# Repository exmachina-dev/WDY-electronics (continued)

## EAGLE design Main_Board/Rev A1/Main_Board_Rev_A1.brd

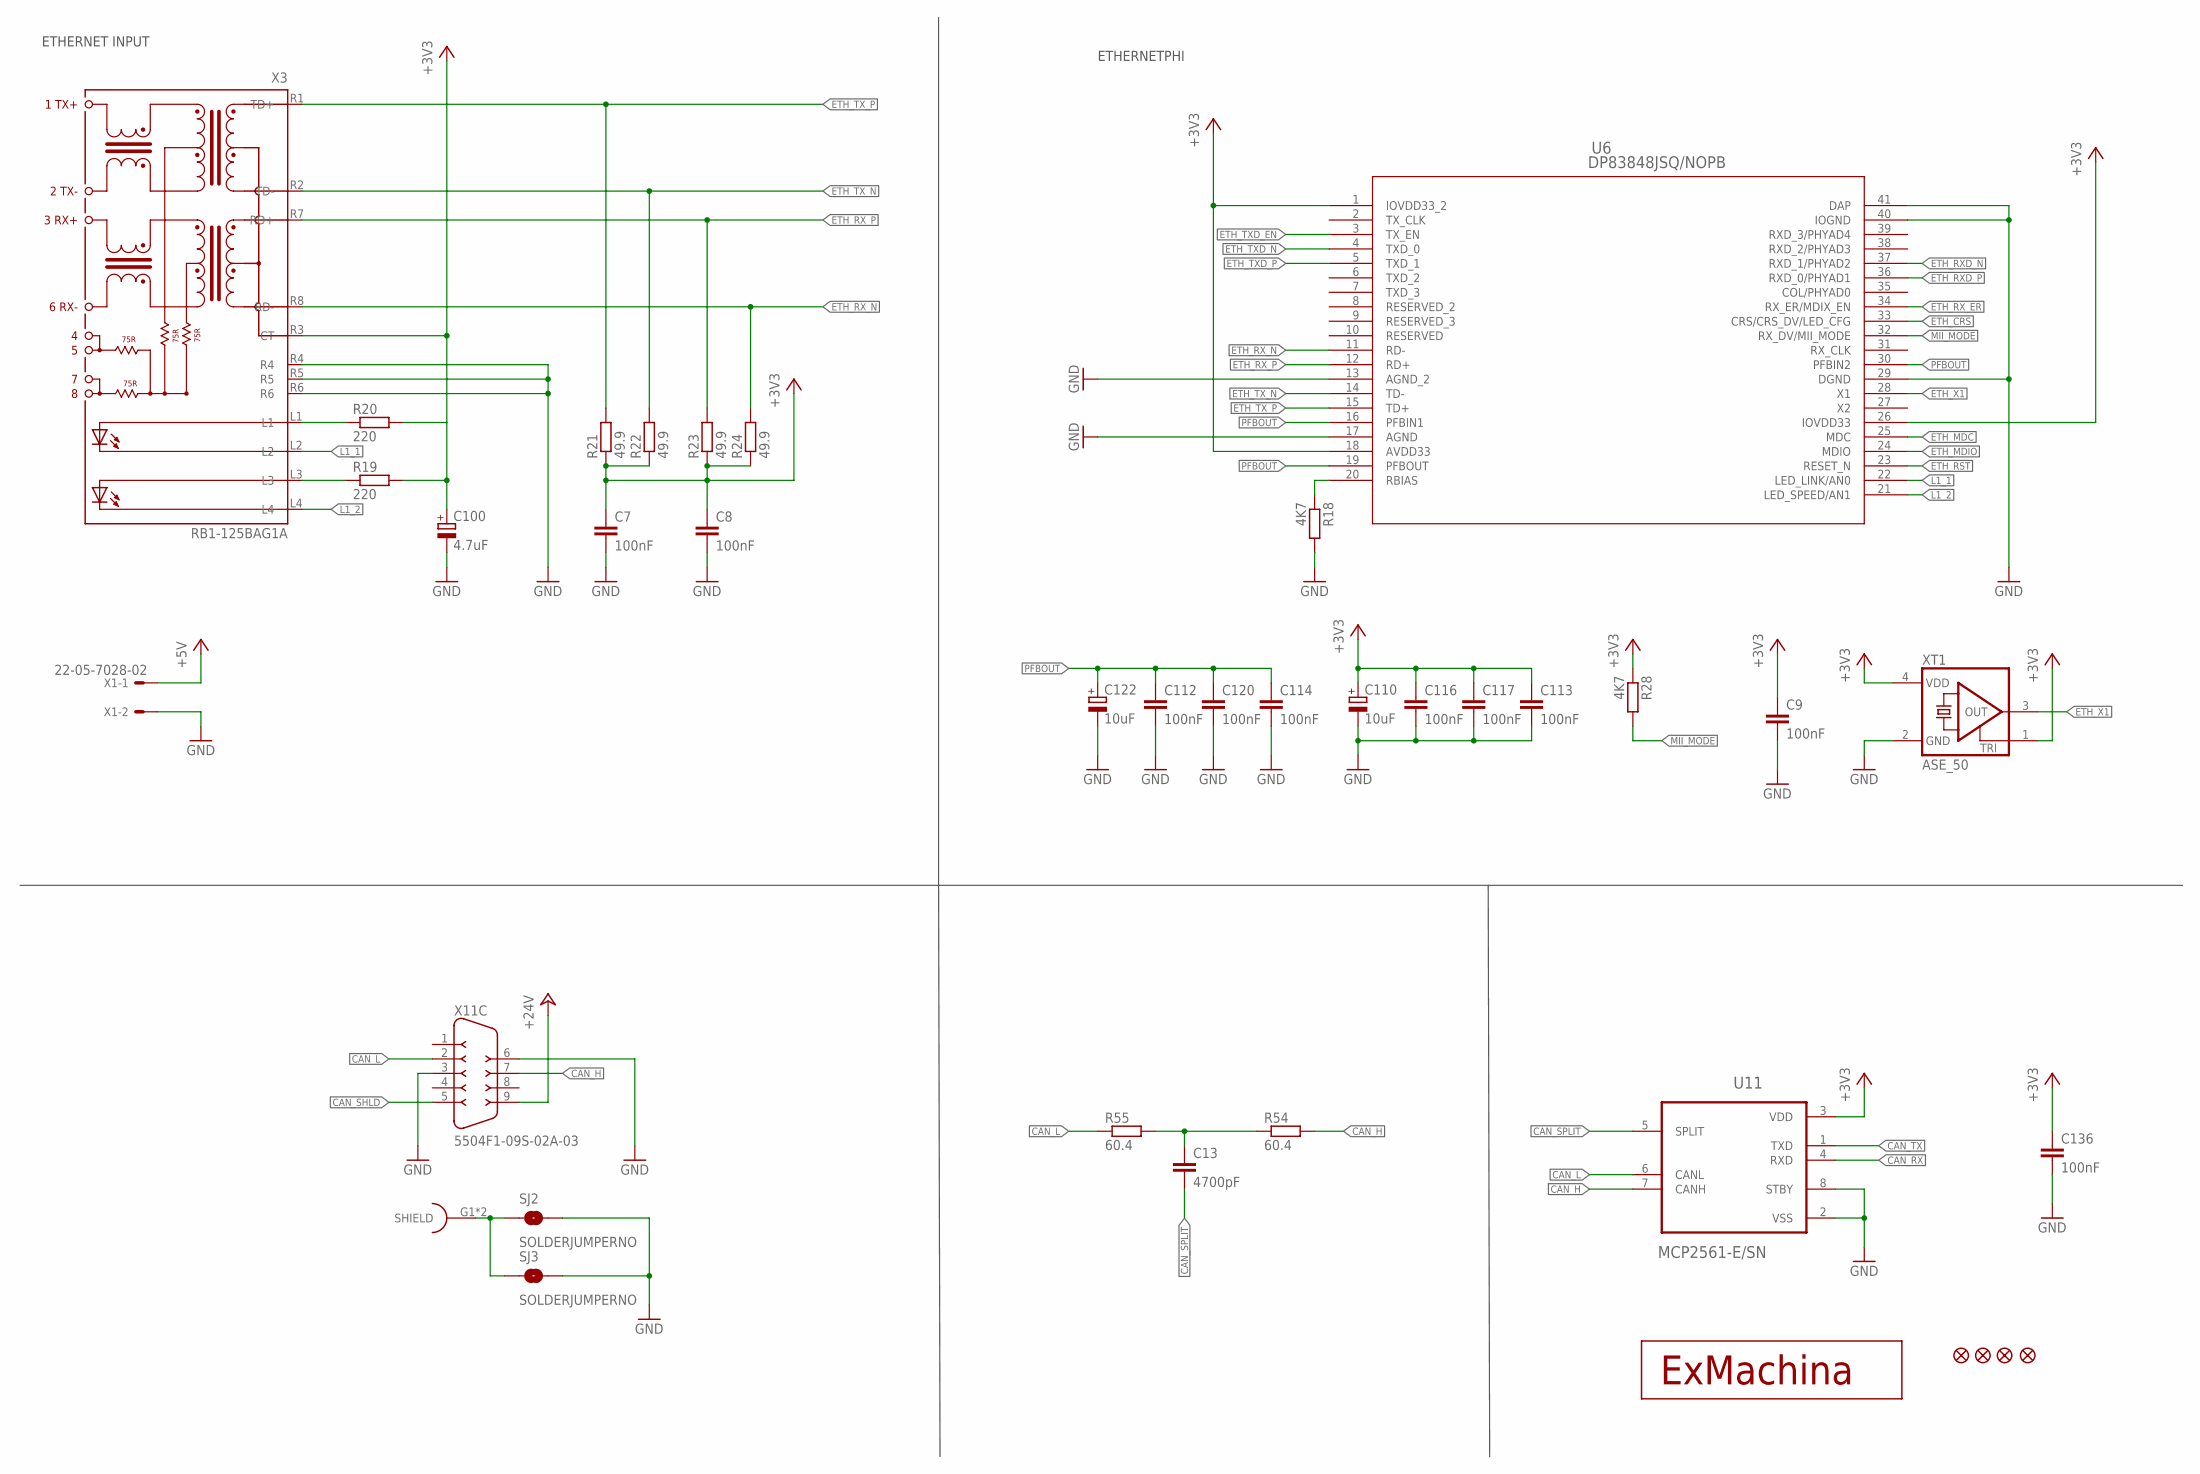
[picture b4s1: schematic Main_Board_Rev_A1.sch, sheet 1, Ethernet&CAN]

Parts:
C7, C8, C9, C112, C113, C114, C116, C117, C120, C136: 100nF; C0603
C13: 4700pF; C0603
C100: 4.7uF; CT3216
C110, C122: 10uF; CT3216
JP1, JP2, JP4, JP5: FIDUCIAL1X2; FIDUCIAL-1X2
R18, R28: 4K7; R0603
R19, R20: 220; R0603
R21, R22, R23, R24: 49.9; R0603
R54, R55: 60.4; R0603
SJ2, SJ3: SOLDERJUMPERNO; SJ_2S-NO
U6: DP83848JSQ/NOPB; SQA40B
U11: MCP2561-E/SN; SOIC127P600X175-8N
U$2: EXMACHINA-LOGO-NAME; EXM-LOGO-BASELINE
X1: 22-05-7028-02; 7395-02
X3: RB1-125BAG1A; WIZNET_RB1-125BAG1A
X11: 5504F1-09S-02A-03; 5504F1-09S-02A
XT1: ASE_50; ASE

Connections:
+3V3: C7.1, C8.1, C9.1, C100.+, C110.+, C113.1, C116.1, C117.1, C136.1, R19.2, R20.2, R21.1, R22.1, R23.1, R24.1, R28.1, U6.1 (IOVDD33_2), U6.18 (AVDD33), U6.26 (IOVDD33), U11.3 (VDD), X3.R3 (CT), XT1.1 (TRI), XT1.4 (VDD); also elsewhere on the board
+5V: X1.1; also elsewhere on the board
+24V: X11.9; also elsewhere on the board
CAN_H: R54.2, U11.7 (CANH), X11.7
CAN_L: R55.1, U11.6 (CANL), X11.2
CAN_RX: U11.4 (RXD); also elsewhere on the board
CAN_SHLD: X11.5
CAN_SPLIT: C13.2, U11.5 (SPLIT)
CAN_TX: U11.1 (TXD); also elsewhere on the board
ETH_CRS: U6.33 (CRS/CRS_DV/LED_CFG); also elsewhere on the board
ETH_MDC: U6.25 (MDC); also elsewhere on the board
ETH_MDIO: U6.24 (MDIO); also elsewhere on the board
ETH_RST: U6.23 (RESET_N)
ETH_RXD_N: U6.37 (RXD_1/PHYAD2); also elsewhere on the board
ETH_RXD_P: U6.36 (RXD_0/PHYAD1); also elsewhere on the board
ETH_RX_ER: U6.34 (RX_ER/MDIX_EN); also elsewhere on the board
ETH_RX_N: R24.2, U6.11 (RD-), X3.R8 (RD-)
ETH_RX_P: R23.2, U6.12 (RD+), X3.R7 (RD+)
ETH_TXD_EN: U6.3 (TX_EN); also elsewhere on the board
ETH_TXD_N: U6.4 (TXD_0); also elsewhere on the board
ETH_TXD_P: U6.5 (TXD_1); also elsewhere on the board
ETH_TX_N: R22.2, U6.14 (TD-), X3.R2 (TD-)
ETH_TX_P: R21.2, U6.15 (TD+), X3.R1 (TD+)
ETH_X1: U6.28 (X1), XT1.3 (OUT)
GND: C7.2, C8.2, C9.2, C100.-, C110.-, C112.2, C113.2, C114.2, C116.2, C117.2, C120.2, C122.-, C136.2, R18.2, SJ2.2, SJ3.2, U6.13 (AGND_2), U6.17 (AGND), U6.29 (DGND), U6.40 (IOGND), U6.41 (DAP), U11.2 (VSS), U11.8 (STBY), X1.2, X3.R4, X3.R5, X3.R6, X11.3, X11.6, XT1.2 (GND); also elsewhere on the board
L1_1: U6.22 (LED_LINK/AN0), X3.L2
L1_2: U6.21 (LED_SPEED/AN1), X3.L4
MII_MODE: R28.2, U6.32 (RX_DV/MII_MODE)
unnamed: C13.1, R54.1, R55.2
unnamed: R18.1, U6.20 (RBIAS)
unnamed: SJ2.1, SJ3.1, X11.G1 (SHIELD), X11.G2 (SHIELD)
unnamed: R20.1, X3.L1
unnamed: R19.1, X3.L3
PFBOUT: C112.1, C114.1, C120.1, C122.+, U6.16 (PFBIN1), U6.19 (PFBOUT), U6.30 (PFBIN2)

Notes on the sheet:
ETHERNET INPUT
ETHERNETPHI

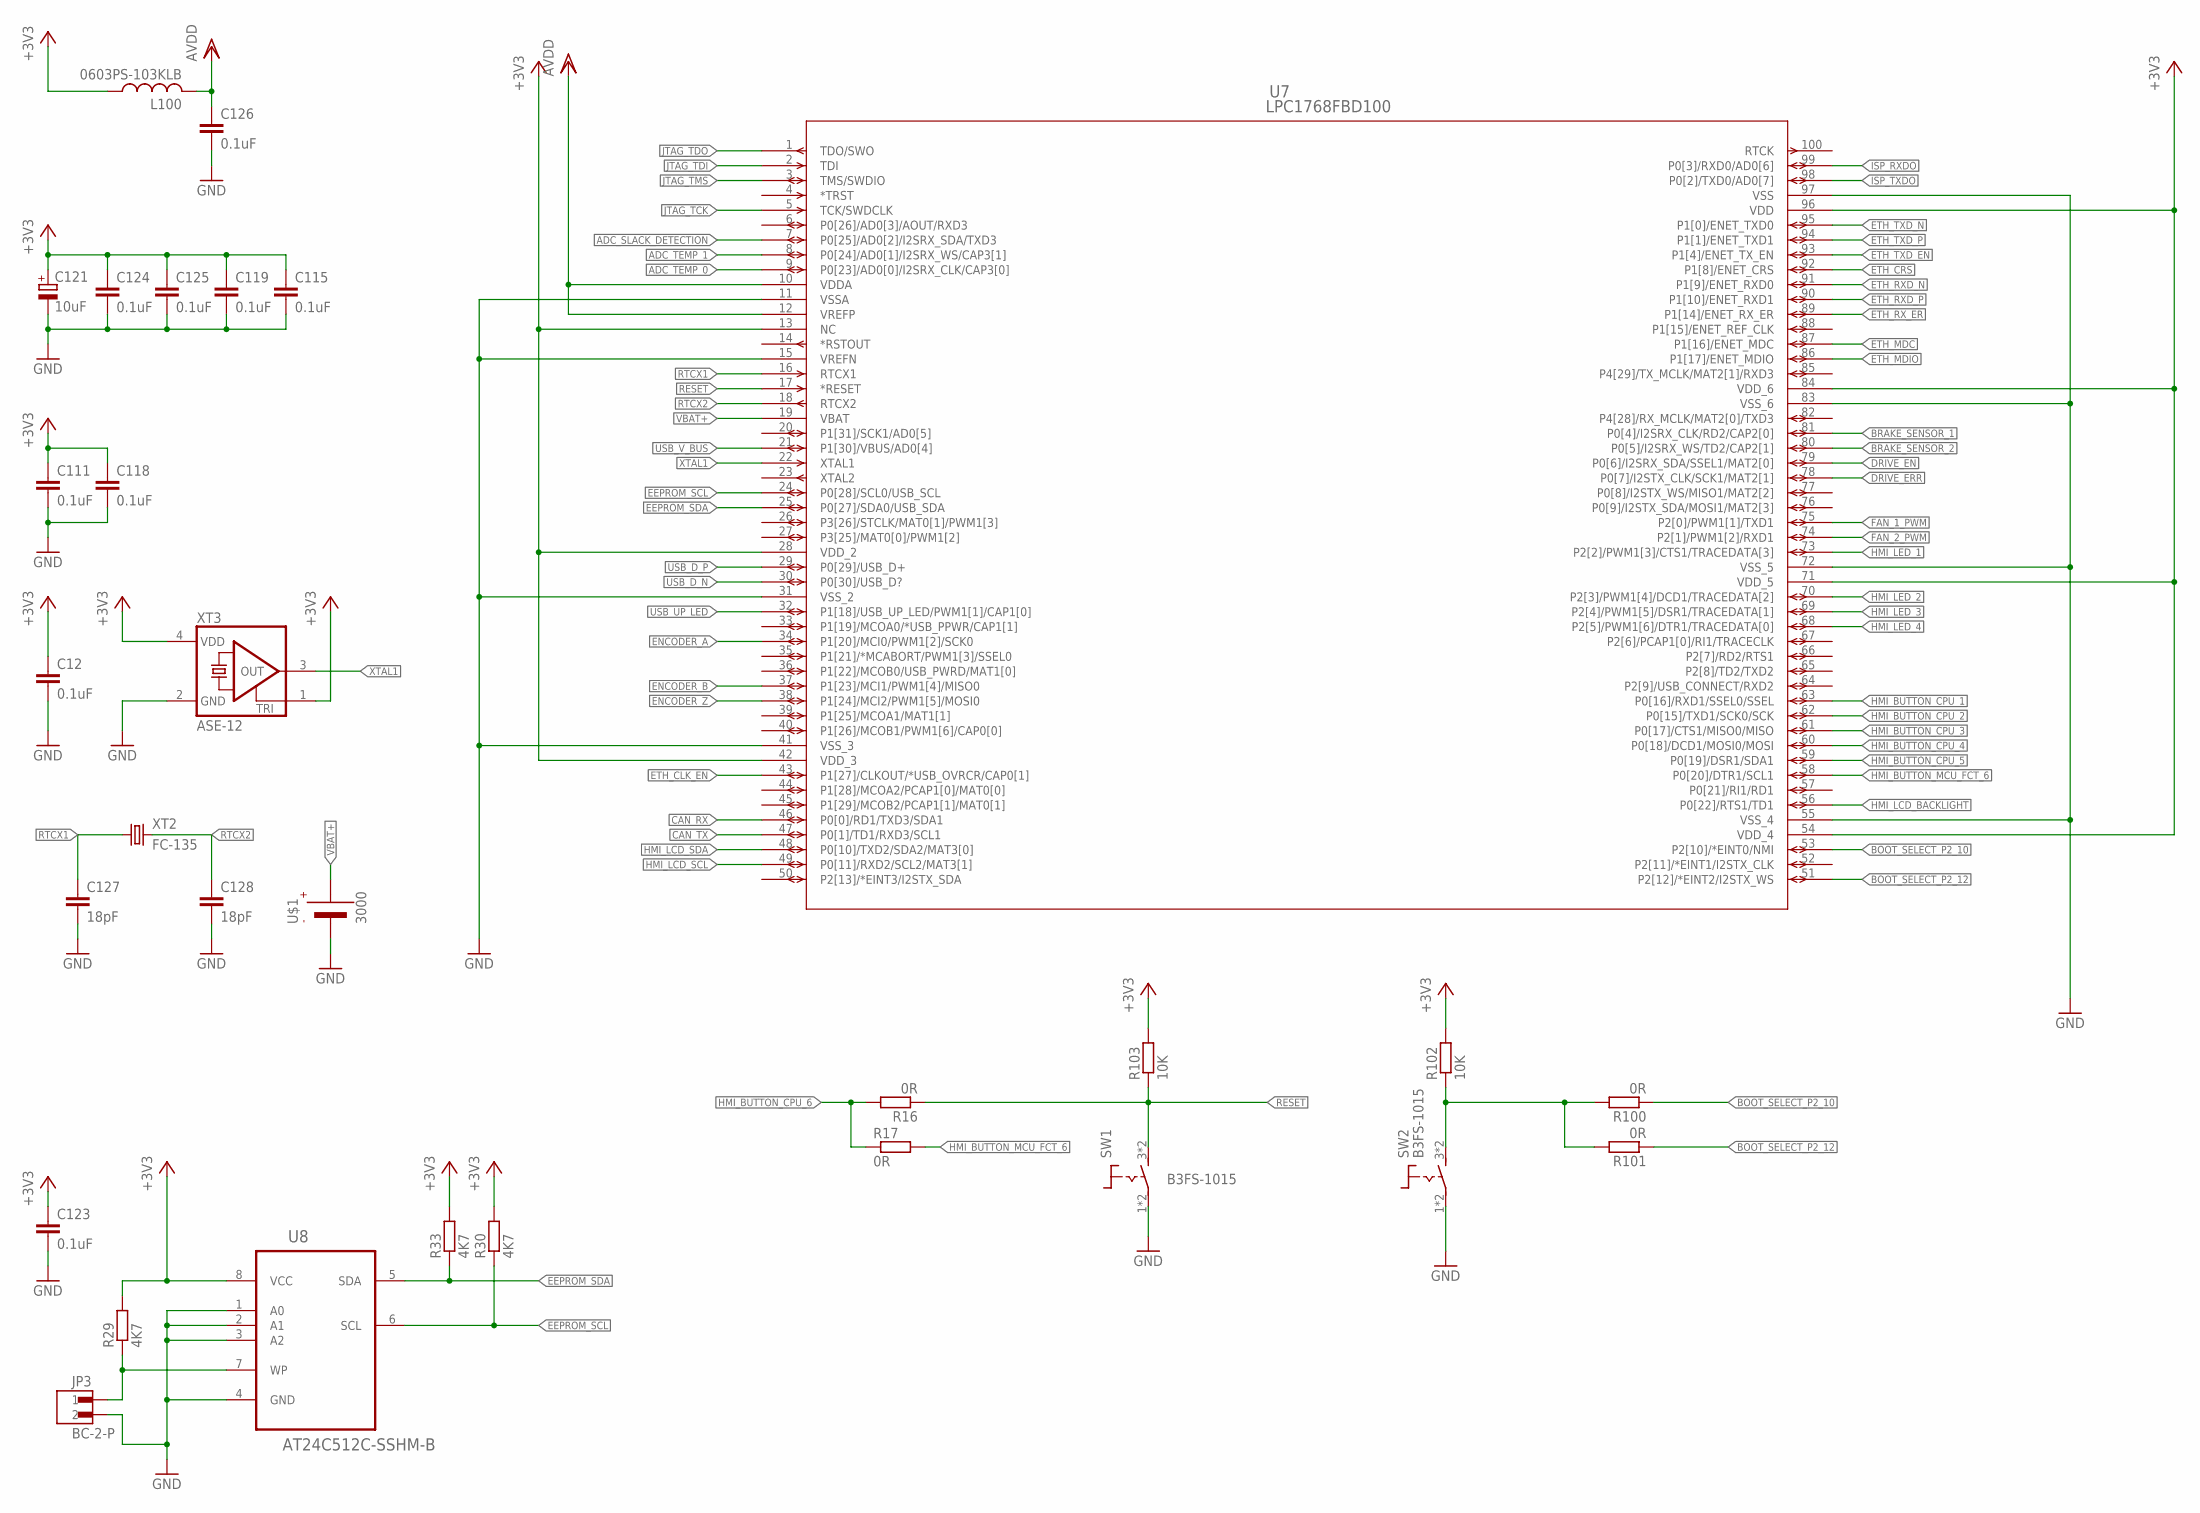
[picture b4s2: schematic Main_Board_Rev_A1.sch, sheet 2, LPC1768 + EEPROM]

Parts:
C12, C111, C115, C118, C119, C123, C124, C125, C126: 0.1uF; C0603
C121: 10uF; CT3216
C127, C128: 18pF; C0603
JP3: BC-2-P
L100: 0603PS-103KLB; 0603
R16, R17, R100, R101: 0R; R0603
R29, R30, R33: 4K7; R0603
R102, R103: 10K; R0603
SW1, SW2: B3FS-1015; B3FS
U7: LPC1768FBD100; SOT407-1
U8: AT24C512C-SSHM-B; SOIC127P600X175-8N
U$1: 3000
XT2: FC-135
XT3: ASE-12; ASE

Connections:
+3V3: C12.1, C111.1, C115.1, C118.1, C119.1, C121.+, C123.1, C124.1, C125.1, L100.P$1 (1), R29.2, R30.2, R33.2, R102.2, R103.2, U7.13 (NC), U7.28 (VDD_2), U7.42 (VDD_3), U7.54 (VDD_4), U7.71 (VDD_5), U7.84 (VDD_6), U7.96 (VDD), U8.8 (VCC), XT3.1 (TRI), XT3.4 (VDD); also elsewhere on the board
ADC_SLACK_DETECTION: U7.7 (P0[25]/AD0[2]/I2SRX_SDA/TXD3); also elsewhere on the board
ADC_TEMP_0: U7.9 (P0[23]/AD0[0]/I2SRX_CLK/CAP3[0]); also elsewhere on the board
ADC_TEMP_1: U7.8 (P0[24]/AD0[1]/I2SRX_WS/CAP3[1]); also elsewhere on the board
AVDD: C126.1, L100.P$2 (2), U7.10 (VDDA), U7.12 (VREFP); also elsewhere on the board
BOOT_SELECT_P2_10: R100.1, U7.53 (P2[10]/*EINT0/NMI)
BOOT_SELECT_P2_12: R101.1, U7.51 (P2[12]/*EINT2/I2STX_WS)
BRAKE_SENSOR_1: U7.81 (P0[4]/I2SRX_CLK/RD2/CAP2[0]); also elsewhere on the board
BRAKE_SENSOR_2: U7.80 (P0[5]/I2SRX_WS/TD2/CAP2[1]); also elsewhere on the board
CAN_RX: U7.46 (P0[0]/RD1/TXD3/SDA1); also elsewhere on the board
CAN_TX: U7.47 (P0[1]/TD1/RXD3/SCL1); also elsewhere on the board
DRIVE_EN: U7.79 (P0[6]/I2SRX_SDA/SSEL1/MAT2[0]); also elsewhere on the board
DRIVE_ERR: U7.78 (P0[7]/I2STX_CLK/SCK1/MAT2[1]); also elsewhere on the board
EEPROM_SCL: R30.1, U7.24 (P0[28]/SCL0/USB_SCL), U8.6 (SCL)
EEPROM_SDA: R33.1, U7.25 (P0[27]/SDA0/USB_SDA), U8.5 (SDA)
ENCODER_A: U7.34 (P1[20]/MCI0/PWM1[2]/SCK0); also elsewhere on the board
ENCODER_B: U7.37 (P1[23]/MCI1/PWM1[4]/MISO0); also elsewhere on the board
ENCODER_Z: U7.38 (P1[24]/MCI2/PWM1[5]/MOSI0); also elsewhere on the board
ETH_CLK_EN: U7.43 (P1[27]/CLKOUT/*USB_OVRCR/CAP0[1])
ETH_CRS: U7.92 (P1[8]/ENET_CRS); also elsewhere on the board
ETH_MDC: U7.87 (P1[16]/ENET_MDC); also elsewhere on the board
ETH_MDIO: U7.86 (P1[17]/ENET_MDIO); also elsewhere on the board
ETH_RXD_N: U7.91 (P1[9]/ENET_RXD0); also elsewhere on the board
ETH_RXD_P: U7.90 (P1[10]/ENET_RXD1); also elsewhere on the board
ETH_RX_ER: U7.89 (P1[14]/ENET_RX_ER); also elsewhere on the board
ETH_TXD_EN: U7.93 (P1[4]/ENET_TX_EN); also elsewhere on the board
ETH_TXD_N: U7.95 (P1[0]/ENET_TXD0); also elsewhere on the board
ETH_TXD_P: U7.94 (P1[1]/ENET_TXD1); also elsewhere on the board
FAN_1_PWM: U7.75 (P2[0]/PWM1[1]/TXD1); also elsewhere on the board
FAN_2_PWM: U7.74 (P2[1]/PWM1[2]/RXD1); also elsewhere on the board
GND: C12.2, C111.2, C115.2, C118.2, C119.2, C121.-, C123.2, C124.2, C125.2, C126.2, C127.2, C128.2, JP3.2, SW1.1 (2), SW1.2, SW2.1 (2), SW2.2, U7.11 (VSSA), U7.15 (VREFN), U7.31 (VSS_2), U7.41 (VSS_3), U7.55 (VSS_4), U7.72 (VSS_5), U7.83 (VSS_6), U7.97 (VSS), U8.1 (A0), U8.2 (A1), U8.3 (A2), U8.4 (GND), U$1.- (VBAT-), XT3.2 (GND); also elsewhere on the board
HMI_BUTTON_CPU_1: U7.63 (P0[16]/RXD1/SSEL0/SSEL); also elsewhere on the board
HMI_BUTTON_CPU_2: U7.62 (P0[15]/TXD1/SCK0/SCK); also elsewhere on the board
HMI_BUTTON_CPU_3: U7.61 (P0[17]/CTS1/MISO0/MISO); also elsewhere on the board
HMI_BUTTON_CPU_4: U7.60 (P0[18]/DCD1/MOSI0/MOSI); also elsewhere on the board
HMI_BUTTON_CPU_5: U7.59 (P0[19]/DSR1/SDA1); also elsewhere on the board
HMI_BUTTON_CPU_6: R16.2, R17.1; also elsewhere on the board
HMI_BUTTON_MCU_FCT_6: R17.2, U7.58 (P0[20]/DTR1/SCL1)
HMI_LCD_BACKLIGHT: U7.56 (P0[22]/RTS1/TD1); also elsewhere on the board
HMI_LCD_SCL: U7.49 (P0[11]/RXD2/SCL2/MAT3[1]); also elsewhere on the board
HMI_LCD_SDA: U7.48 (P0[10]/TXD2/SDA2/MAT3[0]); also elsewhere on the board
HMI_LED_1: U7.73 (P2[2]/PWM1[3]/CTS1/TRACEDATA[3]); also elsewhere on the board
HMI_LED_2: U7.70 (P2[3]/PWM1[4]/DCD1/TRACEDATA[2]); also elsewhere on the board
HMI_LED_3: U7.69 (P2[4]/PWM1[5]/DSR1/TRACEDATA[1]); also elsewhere on the board
HMI_LED_4: U7.68 (P2[5]/PWM1[6]/DTR1/TRACEDATA[0]); also elsewhere on the board
ISP_RXDO: U7.99 (P0[3]/RXD0/AD0[6]); also elsewhere on the board
ISP_TXDO: U7.98 (P0[2]/TXD0/AD0[7]); also elsewhere on the board
JTAG_TCK: U7.5 (TCK/SWDCLK); also elsewhere on the board
JTAG_TDI: U7.2 (TDI); also elsewhere on the board
JTAG_TDO: U7.1 (TDO/SWO); also elsewhere on the board
JTAG_TMS: U7.3 (TMS/SWDIO); also elsewhere on the board
unnamed: R100.2, R101.2, R102.1, SW2.3 (1), SW2.4 (1)
unnamed: JP3.1, R29.1, U8.7 (WP)
RESET: R16.1, R103.1, SW1.3 (1), SW1.4 (1), U7.17 (*RESET); also elsewhere on the board
RTCX1: C127.1, U7.16 (RTCX1), XT2.1
RTCX2: C128.1, U7.18 (RTCX2), XT2.2
USB_D_N: U7.30 (P0[30]/USB_D?); also elsewhere on the board
USB_D_P: U7.29 (P0[29]/USB_D+); also elsewhere on the board
USB_UP_LED: U7.32 (P1[18]/USB_UP_LED/PWM1[1]/CAP1[0]); also elsewhere on the board
USB_V_BUS: U7.21 (P1[30]/VBUS/AD0[4]); also elsewhere on the board
VBAT+: U7.19 (VBAT), U$1.+1 (VBAT+), U$1.+2 (VBAT+)
XTAL1: U7.22 (XTAL1), XT3.3 (OUT)

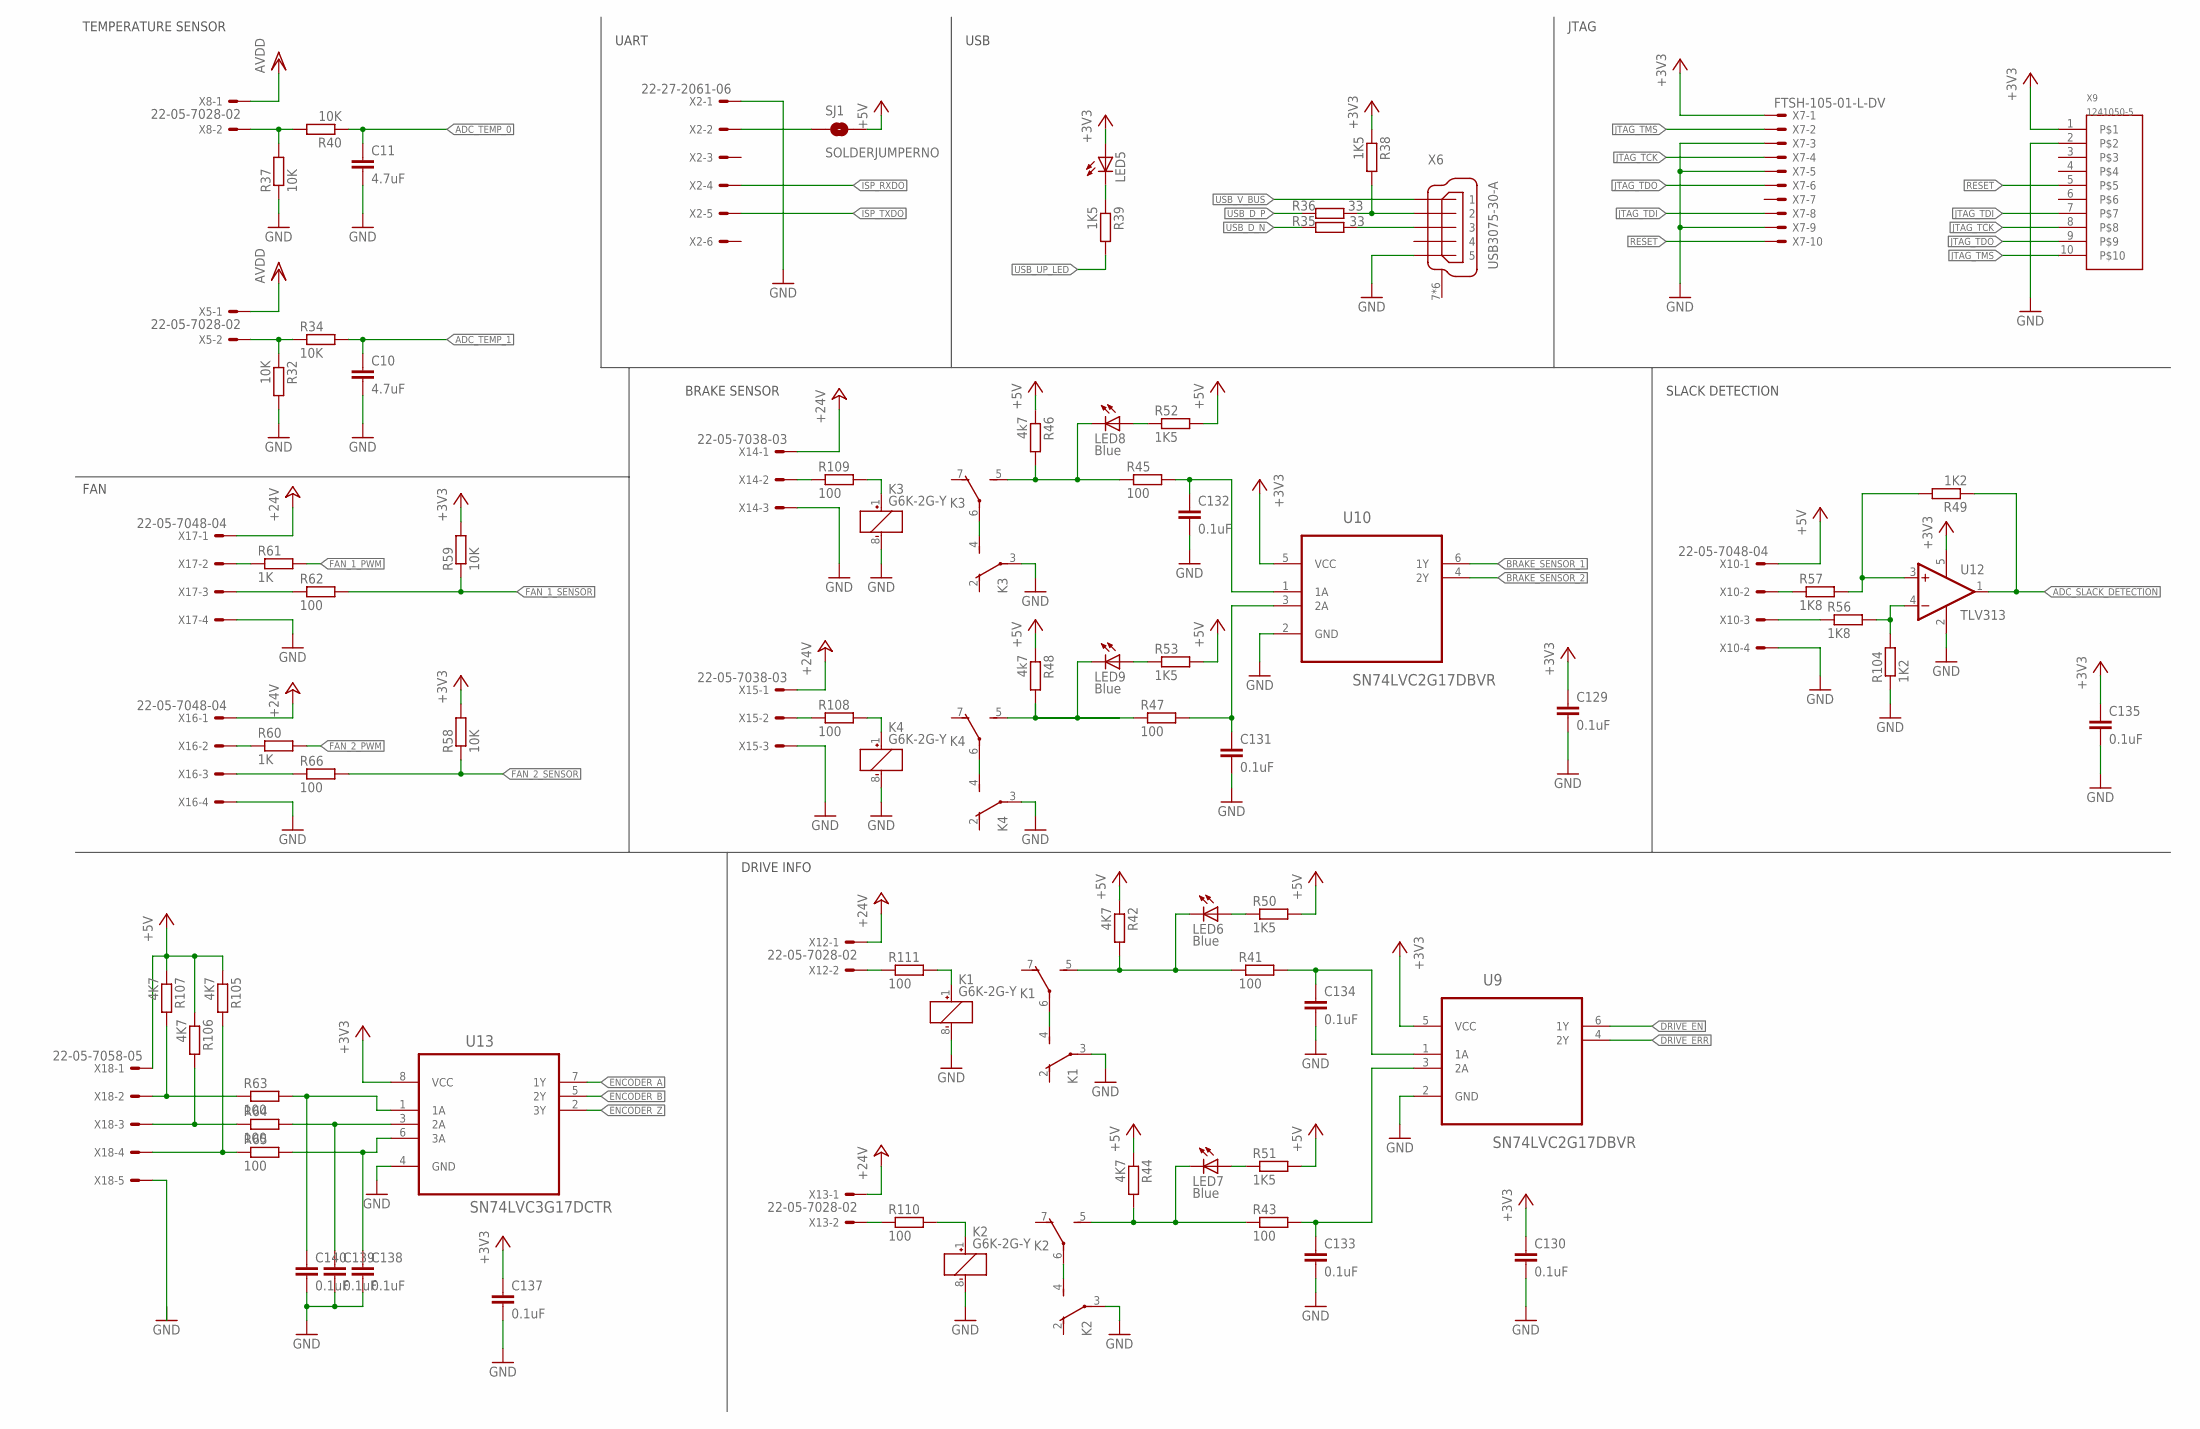
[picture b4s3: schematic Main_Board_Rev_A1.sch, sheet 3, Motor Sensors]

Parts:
C10, C11: 4.7uF; C0603
C129, C130, C131, C132, C133, C134, C135, C137, C138, C139, C140: 0.1uF; C0603
K1, K2, K3, K4: G6K-2G-Y
LED5: LEDCHIPLED_0603; CHIPLED_0603
LED6, LED7, LED8, LED9: Blue; CHIPLED_0603
R32, R34, R37, R40, R58, R59: 10K; R0603
R35, R36: 33; R0603
R38, R39, R50, R51, R52, R53: 1K5; R0603
R41, R43, R45, R47, R62, R63, R64, R65, R66, R108, R109, R110, R111: 100; R0603
R42, R44, R105, R106, R107: 4K7; R0603
R46, R48: 4k7; R0603
R49, R104: 1K2; R0603
R56, R57: 1K8; R0603
R60, R61: 1K; R0603
SJ1: SOLDERJUMPERNO; SJ_2S-NO
U9, U10: SN74LVC2G17DBVR; SOT95P280X145-6N
U12: TLV313; SOT23-DBV
U13: SN74LVC3G17DCTR; SOP65P400X130-8N
X2: 22-27-2061-06; 6410-06
X5, X8, X12, X13: 22-05-7028-02; 7395-02
X6: USB3075-30-A; USB_MICROB_SMT
X7: FTSH-105-01-L-DV
X9: 1241050-5; 2.54/2X5
X10, X16, X17: 22-05-7048-04; 7395-04
X14, X15: 22-05-7038-03; 7395-03
X18: 22-05-7058-05; 7395-05

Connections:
+3V3: C129.1, C130.1, C135.1, C137.1, LED5.A, R38.1, R58.2, R59.2, U9.5 (VCC), U10.5 (VCC), U12.5 (V+), U13.8 (VCC), X7.1, X9.1; also elsewhere on the board
+5V: R42.1, R44.1, R46.1, R48.1, R50.2, R51.2, R52.2, R53.2, R105.1, R106.1, R107.1, SJ1.2, X10.1, X18.1; also elsewhere on the board
+24V: X12.1, X13.1, X14.1, X15.1, X16.1, X17.1; also elsewhere on the board
ADC_SLACK_DETECTION: R49.1, U12.1 (OUT); also elsewhere on the board
ADC_TEMP_0: C11.1, R40.1; also elsewhere on the board
ADC_TEMP_1: C10.1, R34.2; also elsewhere on the board
AVDD: X5.1, X8.1; also elsewhere on the board
BRAKE_SENSOR_1: U10.6 (1Y); also elsewhere on the board
BRAKE_SENSOR_2: U10.4 (2Y); also elsewhere on the board
DRIVE_EN: U9.6 (1Y); also elsewhere on the board
DRIVE_ERR: U9.4 (2Y); also elsewhere on the board
ENCODER_A: U13.7 (1Y); also elsewhere on the board
ENCODER_B: U13.5 (2Y); also elsewhere on the board
ENCODER_Z: U13.2 (3Y); also elsewhere on the board
FAN_1_PWM: R61.2; also elsewhere on the board
FAN_1_SENSOR: R59.1, R62.2
FAN_2_PWM: R60.2; also elsewhere on the board
FAN_2_SENSOR: R58.1, R66.2
GND: C10.2, C11.2, C129.2, C130.2, C131.2, C132.2, C133.2, C134.2, C135.2, C137.2, C138.2, C139.2, C140.2, K1.3, K1.8 (-), K2.3, K2.8 (-), K3.3, K3.8 (-), K4.3, K4.8 (-), R32.2, R37.1, R104.1, U9.2 (GND), U10.2 (GND), U12.2 (V-), U13.4 (GND), X2.1, X6.5, X7.3, X7.5, X7.9, X9.2, X10.4, X14.3, X15.3, X16.4, X17.4; also elsewhere on the board
ISP_RXDO: X2.4; also elsewhere on the board
ISP_TXDO: X2.5; also elsewhere on the board
JTAG_TCK: X7.4, X9.8; also elsewhere on the board
JTAG_TDI: X7.8, X9.7; also elsewhere on the board
JTAG_TDO: X7.6, X9.9; also elsewhere on the board
JTAG_TMS: X7.2, X9.10; also elsewhere on the board
unnamed: R61.1, X17.2
unnamed: R66.1, X16.3
unnamed: R60.1, X16.2
unnamed: R62.1, X17.3
unnamed: R36.1, R38.2, X6.2
unnamed: R35.1, X6.3
unnamed: LED5.C, R39.1
unnamed: R109.1, X14.2
unnamed: R108.1, X15.2
unnamed: K3.1 (+), R109.2
unnamed: K1.1 (+), R111.2
unnamed: K3.4 (S), K3.6
unnamed: R57.1, X10.2
unnamed: R111.1, X12.2
unnamed: K2.1 (+), R110.2
unnamed: R63.1, R107.2, X18.2
unnamed: R110.1, X13.2
unnamed: C131.1, R47.2, U10.3 (2A)
unnamed: C132.1, R45.2, U10.1 (1A)
unnamed: R64.1, R106.2, X18.3
unnamed: C134.1, R41.2, U9.1 (1A)
unnamed: C133.1, R43.2, U9.3 (2A)
unnamed: R65.1, R105.2, X18.4
unnamed: C138.1, R65.2, U13.6 (3A)
unnamed: C139.1, R64.2, U13.3 (2A)
unnamed: C140.1, R63.2, U13.1 (1A)
unnamed: K4.1 (+), R108.2
unnamed: K4.4 (S), K4.6
unnamed: K3.5 (S), LED8.C, R45.1, R46.2
unnamed: K2.4 (S), K2.6
unnamed: K1.4 (S), K1.6
unnamed: R49.2, R57.2, U12.3 (+IN)
unnamed: R37.2, R40.2, X8.2
unnamed: R32.1, R34.1, X5.2
unnamed: R56.2, R104.2, U12.4 (-IN)
unnamed: R56.1, X10.3
unnamed: SJ1.1, X2.2
unnamed: LED8.A, R52.1
unnamed: K4.5 (S), LED9.C, R47.1, R48.2
unnamed: LED9.A, R53.1
unnamed: K1.5 (S), LED6.C, R41.1, R42.2
unnamed: LED6.A, R50.1
unnamed: K2.5 (S), LED7.C, R43.1, R44.2
unnamed: LED7.A, R51.1
RESET: X7.10, X9.5; also elsewhere on the board
USB_D_N: R35.2; also elsewhere on the board
USB_D_P: R36.2; also elsewhere on the board
USB_UP_LED: R39.2; also elsewhere on the board
USB_V_BUS: X6.1; also elsewhere on the board

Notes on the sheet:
USB
JTAG
TEMPERATURE SENSOR
FAN
SLACK DETECTION
BRAKE SENSOR
DRIVE INFO
UART

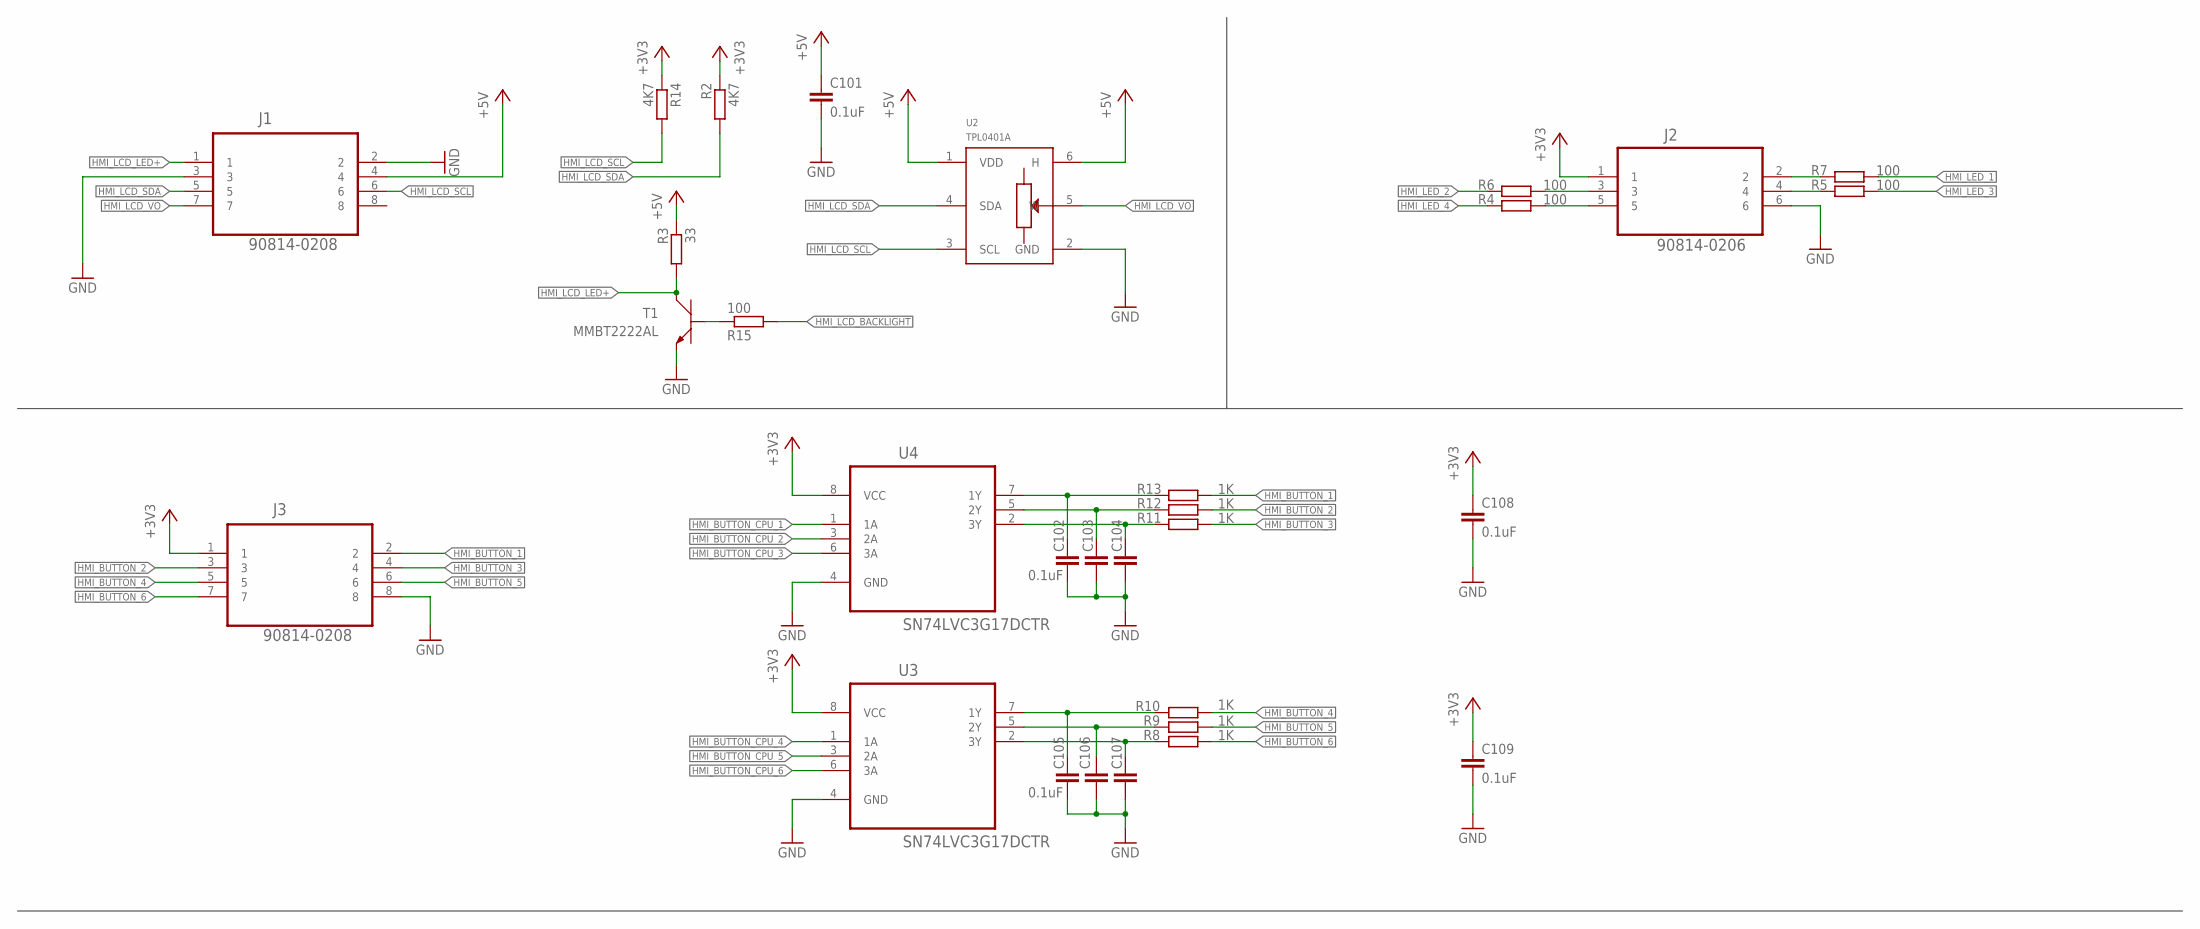
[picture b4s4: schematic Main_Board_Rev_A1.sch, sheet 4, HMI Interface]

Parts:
C101, C102, C103, C104, C105, C106, C107, C108, C109: 0.1uF; C0603
J1, J3: 90814-0208; MOLEX_90814-0208
J2: 90814-0206; MOLEX_90814-0206
R2, R14: 4K7; R0603
R3: 33; R0603
R4, R5, R6, R7, R15: 100; R0603
R8, R9, R10, R11, R12, R13: 1K; R0603
T1: MMBT2222AL; SOT−23
U2: TPL0401A; SC-70-DCK
U3, U4: SN74LVC3G17DCTR; SOP65P400X130-8N

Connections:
+3V3: C108.1, C109.1, J2.1, J3.1, R2.1, R14.1, U3.8 (VCC), U4.8 (VCC); also elsewhere on the board
+5V: C101.1, J1.4, R3.1, U2.1 (VDD), U2.6 (H); also elsewhere on the board
GND: C101.2, C102.2, C103.2, C104.2, C105.2, C106.2, C107.2, C108.2, C109.2, J1.2, J1.3, J2.6, J3.8, T1.2 (E), U2.2 (GND), U3.4 (GND), U4.4 (GND); also elsewhere on the board
HMI_BUTTON_1: J3.2, R13.1
HMI_BUTTON_2: J3.3, R12.1
HMI_BUTTON_3: J3.4, R11.1
HMI_BUTTON_4: J3.5, R10.1
HMI_BUTTON_5: J3.6, R9.1
HMI_BUTTON_6: J3.7, R8.1
HMI_BUTTON_CPU_1: U4.1 (1A); also elsewhere on the board
HMI_BUTTON_CPU_2: U4.3 (2A); also elsewhere on the board
HMI_BUTTON_CPU_3: U4.6 (3A); also elsewhere on the board
HMI_BUTTON_CPU_4: U3.1 (1A); also elsewhere on the board
HMI_BUTTON_CPU_5: U3.3 (2A); also elsewhere on the board
HMI_BUTTON_CPU_6: U3.6 (3A); also elsewhere on the board
HMI_LCD_BACKLIGHT: R15.2; also elsewhere on the board
HMI_LCD_LED+: J1.1, R3.2, T1.3 (C)
HMI_LCD_SCL: J1.6, R14.2, U2.3 (SCL); also elsewhere on the board
HMI_LCD_SDA: J1.5, R2.2, U2.4 (SDA); also elsewhere on the board
HMI_LCD_VO: J1.7, U2.5 (W)
HMI_LED_1: R7.1; also elsewhere on the board
HMI_LED_2: R6.2; also elsewhere on the board
HMI_LED_3: R5.1; also elsewhere on the board
HMI_LED_4: R4.2; also elsewhere on the board
unnamed: J2.3, R6.1
unnamed: J2.5, R4.1
unnamed: R15.1, T1.1 (B)
unnamed: C102.1, R13.2, U4.7 (1Y)
unnamed: C103.1, R12.2, U4.5 (2Y)
unnamed: C104.1, R11.2, U4.2 (3Y)
unnamed: C105.1, R10.2, U3.7 (1Y)
unnamed: C106.1, R9.2, U3.5 (2Y)
unnamed: C107.1, R8.2, U3.2 (3Y)
unnamed: J2.2, R7.2
unnamed: J2.4, R5.2

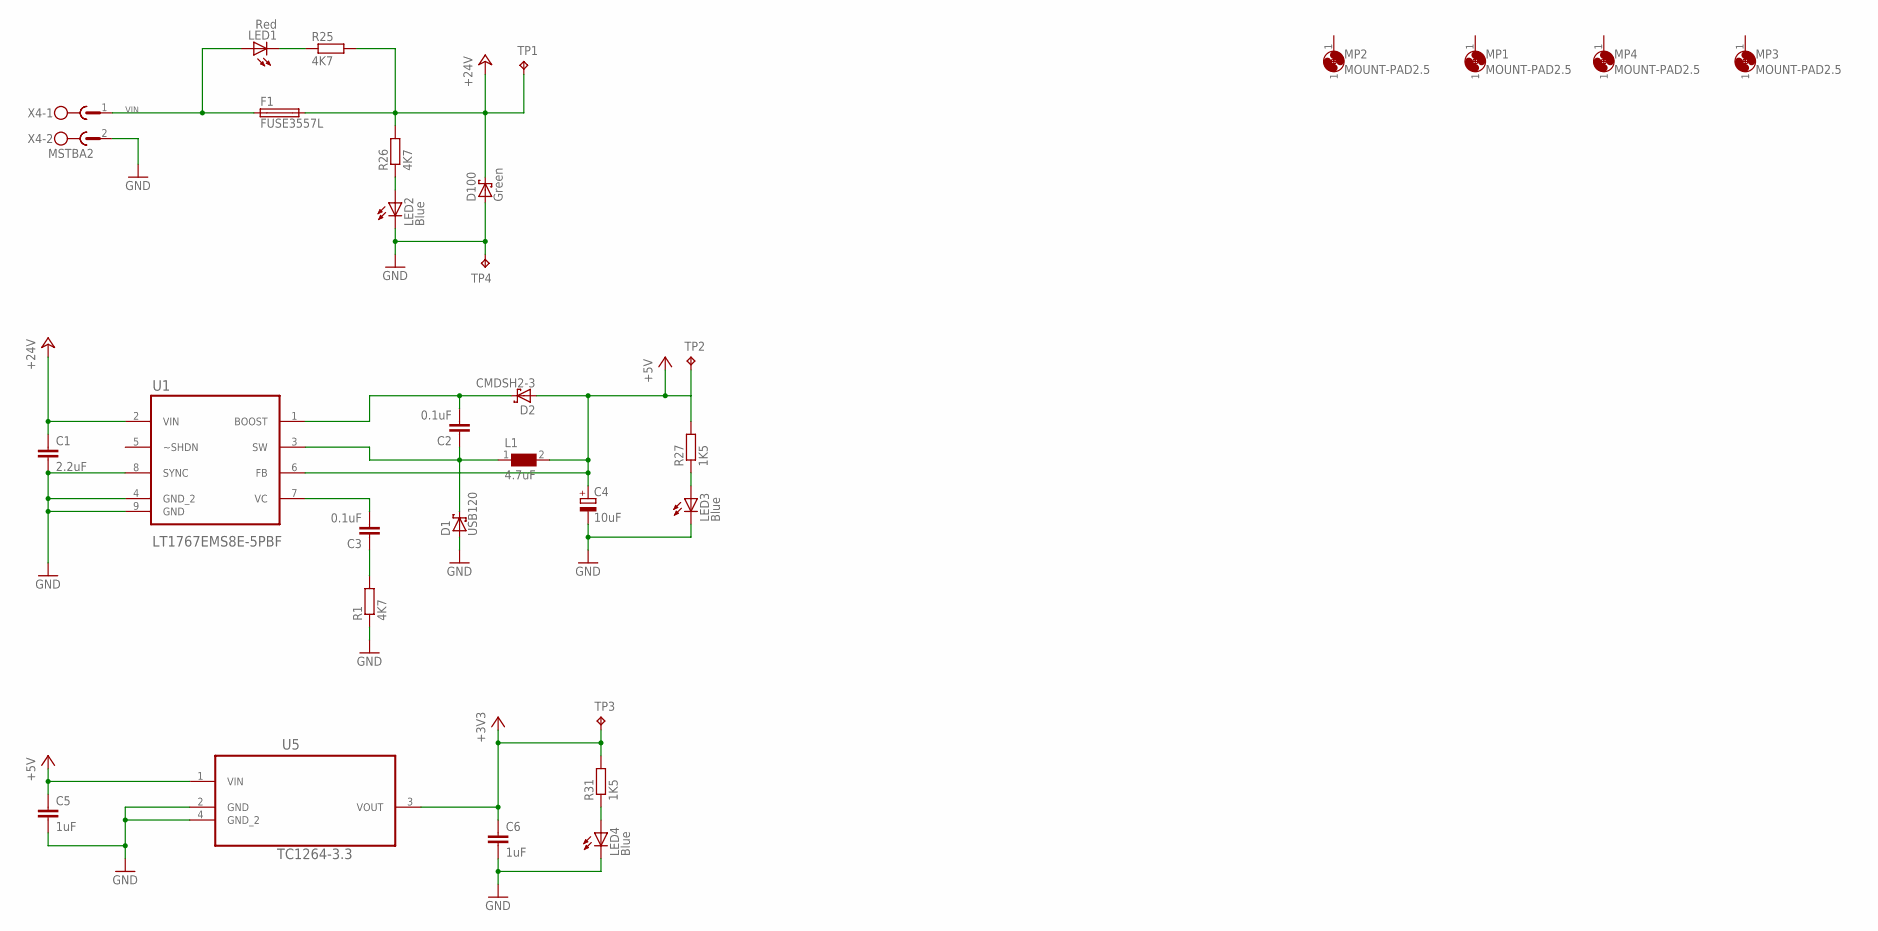
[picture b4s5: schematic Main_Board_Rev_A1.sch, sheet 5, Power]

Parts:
C1: 2.2uF; C0603
C2, C3: 0.1uF; C0603
C4: 10uF; CT3216
C5, C6: 1uF; C0603
D1: USB120; DO216AA
D2: CMDSH2-3; SOD323-W
D100: Green; SMB
F1: FUSE3557L; 3557-LITTLE
L1: 4.7uF; WE-PD_1030/1050
LED1: Red; CHIPLED_0603
LED2: Blue; CHIPLED_0603
LED3, LED4: Blue; CHIP-LED0603; MPN OVS-0604
MP1, MP2, MP3, MP4: MOUNT-PAD2.5; P2.5
R1, R25, R26: 4K7; R0603
R27, R31: 1K5; R0603; MPN MCMR06X1501FTL
TP1, TP2, TP3, TP4: TPB1,27; B1,27
U1: LT1767EMS8E-5PBF; SOP65P490X110-9N
U5: TC1264-3.3; SOT230P700X180-4N
X4: MSTBA2

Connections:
+3V3: C6.1, R31.2, TP3.TP, U5.3 (VOUT); also elsewhere on the board
+5V: C4.+, C5.1, D2.A, L1.2, R27.2, TP2.TP, U1.6 (FB), U5.1 (VIN); also elsewhere on the board
+24V: C1.1, D100.C, F1.3 (2), F1.4 (2), R25.2, R26.2, TP1.TP, U1.2 (VIN); also elsewhere on the board
GND: C1.2, C4.-, C5.2, C6.2, D1.A, D100.A, LED2.C, LED3.C, LED4.C, R1.1, TP4.TP, U1.4 (GND_2), U1.8 (SYNC), U1.9 (GND), U5.2 (GND), U5.4 (GND_2), X4.2; also elsewhere on the board
unnamed: C2.2, D2.C, U1.1 (BOOST)
unnamed: LED2.A, R26.1
unnamed: LED1.C, R25.1
unnamed: C3.1, R1.2
unnamed: C3.2, U1.7 (VC)
unnamed: C2.1, D1.C, L1.1, U1.3 (SW)
unnamed: LED4.A, R31.1
unnamed: LED3.A, R27.1
VIN: F1.1, F1.2 (1), LED1.A, X4.1
